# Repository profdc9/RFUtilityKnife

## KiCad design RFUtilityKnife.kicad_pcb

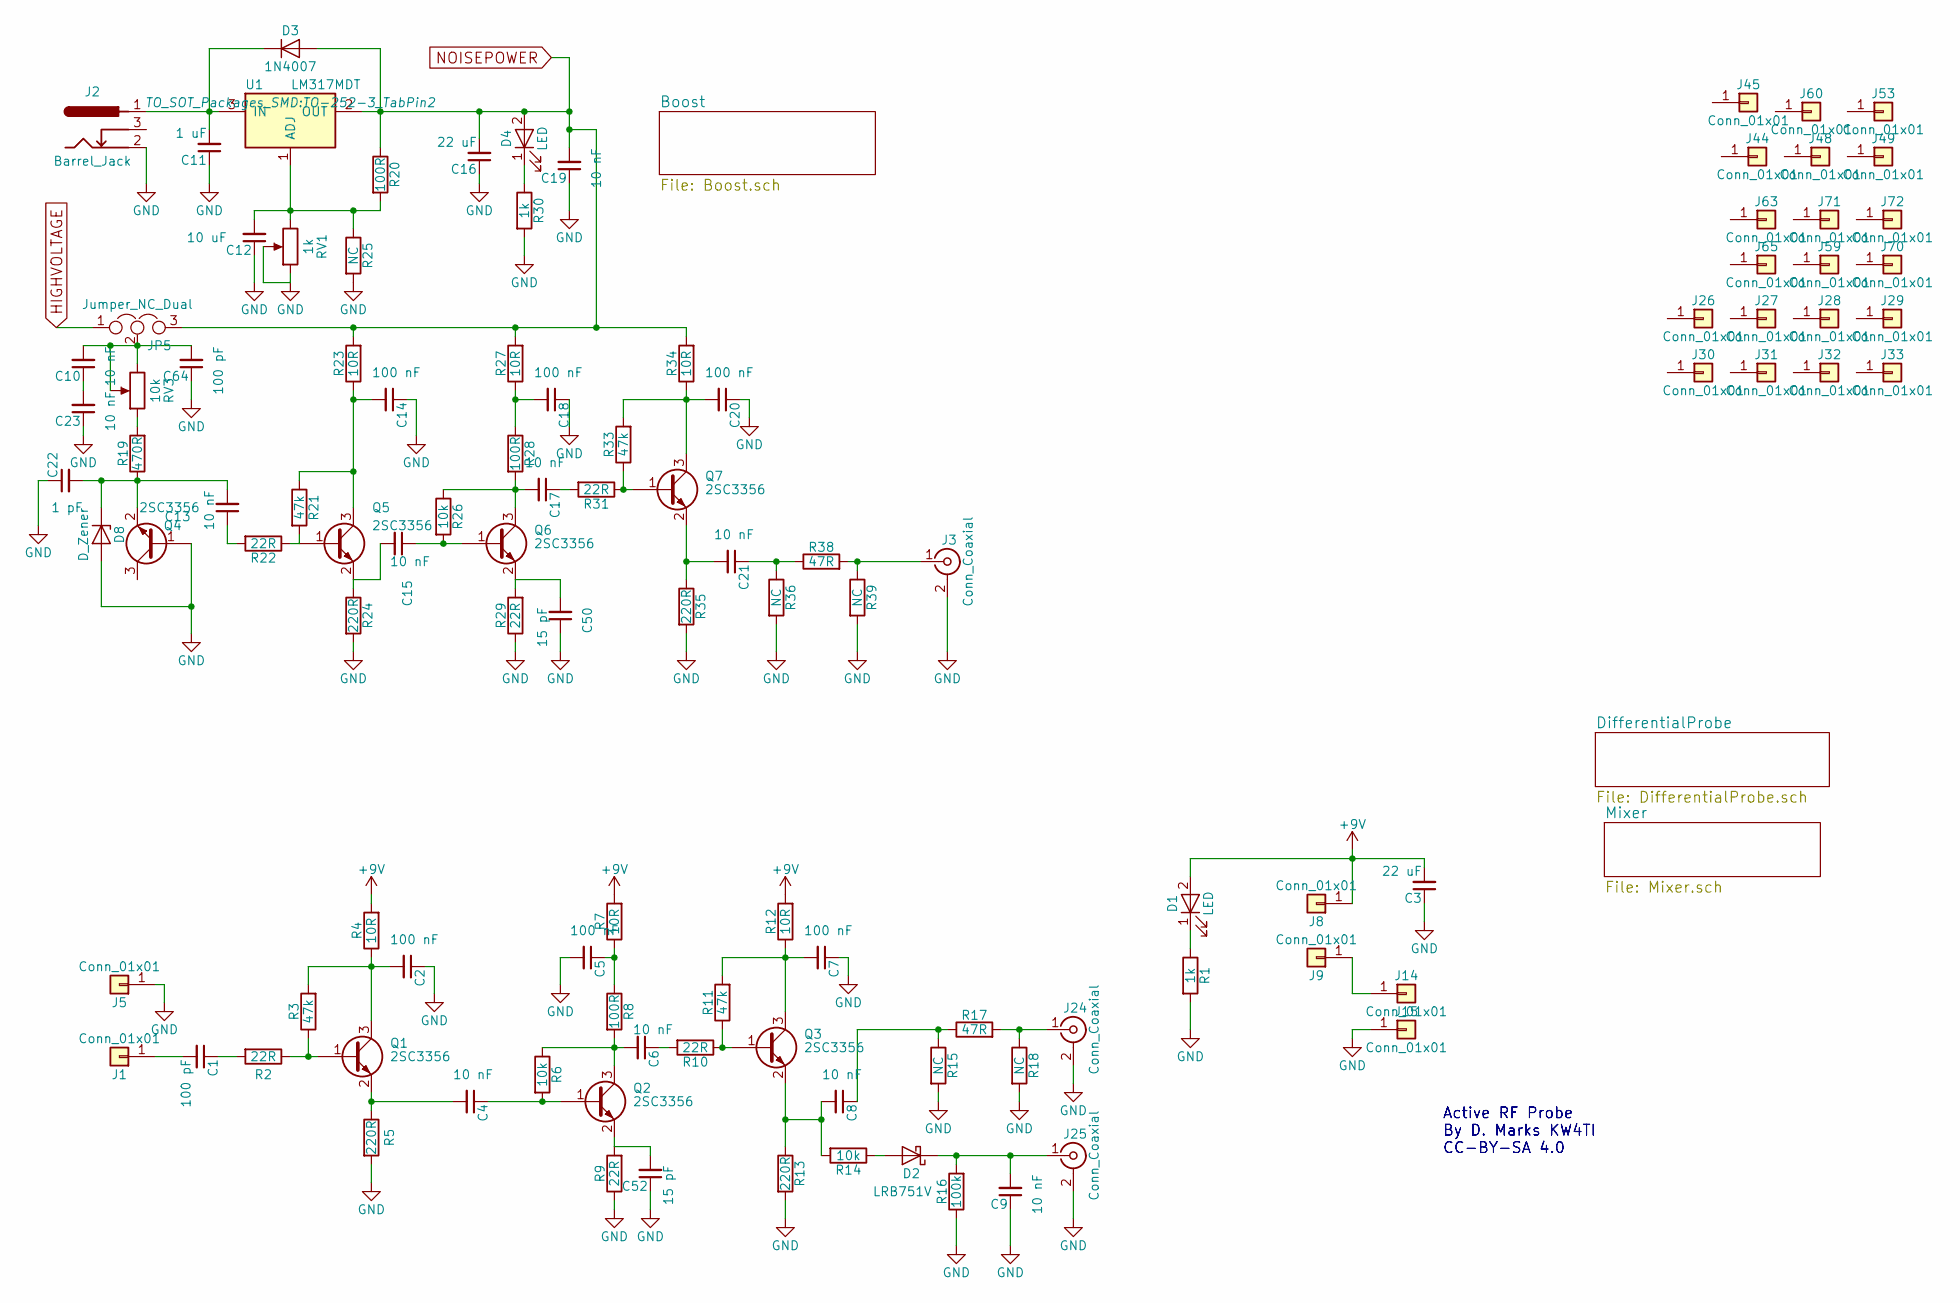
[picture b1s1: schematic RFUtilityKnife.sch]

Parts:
C1, C64: 100 pF; C_0805_HandSoldering; LCSC C1790
C2, C5, C7, C14, C18, C20: 100 nF; C_0805_HandSoldering; LCSC C49678
C3, C16: 22 uF; C_0805_HandSoldering; LCSC C45783
C4, C6, C8, C9, C10, C13, C15, C17, C19, C21, C23: 10 nF; C_0805_HandSoldering; LCSC C1710
C11: 1 uF; C_0805_HandSoldering; LCSC C28323
C12: 10 uF; C_0805_HandSoldering; LCSC C15850
C22: 1 pF; C_0805_HandSoldering; LCSC C14971
C50, C52: 15 pF; C_0805_HandSoldering; LCSC C1794
D1, D4: LED; LED_0805_HandSoldering; LCSC C2296
D2: LRB751V; D_SOD-323_HandSoldering; LCSC C131730
D3: 1N4007; D_SMA_Handsoldering; LCSC C95872
D8: D_Zener; D_MiniMELF
J1, J5, J8, J9, J14, J15: Conn_01x01; PadHole
J2: Barrel_Jack; BARREL_JACK
J3, J24, J25: Conn_Coaxial; Amphenol_RF_SMA_132289
J26, J27, J28, J29, J30, J31, J32, J33, J44, J45, J48, J49, J53, J59, J60, J63, J65, J70, J71, J72: Conn_01x01; BigSlot
JP5: Jumper_NC_Dual; Pin_Header_Straight_1x03_Pitch2.54mm
Q1, Q2, Q3, Q4, Q5, Q6, Q7: 2SC3356; SOT-23; LCSC C9659
R1, R30: 1k; R_0805_HandSoldering; LCSC C17513
R2, R9, R10, R22, R29, R31: 22R; R_0805_HandSoldering; LCSC C17561
R3, R11, R21, R33: 47k; R_0805_HandSoldering; LCSC C17713
R4, R7, R12, R23, R27, R34: 10R; R_0805_HandSoldering; LCSC C17415
R5, R13, R24, R35: 220R; R_0805_HandSoldering; LCSC C17557
R6, R14, R26: 10k; R_0805_HandSoldering; LCSC C17414
R8, R20, R28: 100R; R_0805_HandSoldering; LCSC C17408
R15, R18, R25, R36, R39: NC; R_0805_HandSoldering
R16: 100k; R_0805_HandSoldering; LCSC C17407
R17, R38: 47R; R_0805_HandSoldering; LCSC C17714
R19: 470R; R_0805_HandSoldering; LCSC C17710
RV1: 1k; Potentiometer_Triwood_RM-065
RV3: 10k; Potentiometer_Triwood_RM-065
U1: LM317MDT; TO-252-3_TabPin2; LCSC C75510

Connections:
+9V: C3.2, D1.2 (A), J8.1, R4.2, R7.2, R12.2
GND: C2.1, C3.1, C5.2, C7.1, C9.1, C11.1, C12.1, C14.1, C16.1, C18.1, C19.1, C20.1, C22.1, C23.1, C50.1, C52.1, C64.1, D8.2 (A), J2.2, J3.2 (Ext), J5.1, J15.1, J24.2 (Ext), J25.2 (Ext), Q4.1 (B), R1.2, R5.2, R9.1, R13.2, R15.2, R16.1, R18.2, R24.2, R25.2, R29.1, R30.2, R35.2, R36.2, R39.2, RV1.1, RV1.2; also elsewhere on the board
HIGHVOLTAGE: JP5.1; also elsewhere on the board
NOISEPOWER: C16.2, C19.2, D3.2 (A), D4.2 (A), JP5.3, R20.1, R23.2, R27.2, R34.2, U1.2 (OUT); also elsewhere on the board
unnamed: C1.1, R2.2
unnamed: C1.2, J1.1
unnamed: C2.2, Q1.3 (C), R3.2, R4.1
unnamed: C4.1, Q2.1 (B), R6.2
unnamed: C4.2, Q1.2 (E), R5.1
unnamed: C5.1, R7.1, R8.1
unnamed: C6.1, R10.2
unnamed: C6.2, Q2.3 (C), R6.1, R8.2
unnamed: C7.2, Q3.3 (C), R11.2, R12.1
unnamed: C8.1, R15.1, R17.1
unnamed: C8.2, Q3.2 (E), R13.1, R14.2
unnamed: C9.2, D2.1 (K), J25.1 (In), R16.2
unnamed: C10.1, C23.2
unnamed: C10.2, C64.2, JP5.2, RV3.2, RV3.3
unnamed: C11.2, D3.1 (K), J2.1, U1.3 (IN)
unnamed: C12.2, R20.2, R25.1, RV1.3, U1.1 (ADJ)
unnamed: C13.1, R22.2
unnamed: C13.2, C22.2, D8.1 (K), Q4.2 (E), R19.1
unnamed: C14.2, Q5.3 (C), R21.1, R23.1
unnamed: C15.1, Q6.1 (B), R26.2
unnamed: C15.2, Q5.2 (E), R24.1
unnamed: C17.1, R31.2
unnamed: C17.2, Q6.3 (C), R26.1, R28.2
unnamed: C18.2, R27.1, R28.1
unnamed: C20.2, Q7.3 (C), R33.2, R34.1
unnamed: C21.1, R36.1, R38.1
unnamed: C21.2, Q7.2 (E), R35.1
unnamed: C50.2, Q6.2 (E), R29.2
unnamed: C52.2, Q2.2 (E), R9.2
unnamed: D1.1 (K), R1.1
unnamed: D2.2 (A), R14.1
unnamed: D4.1 (K), R30.1
unnamed: J3.1 (In), R38.2, R39.1
unnamed: J9.1, J14.1
unnamed: J24.1 (In), R17.2, R18.1
unnamed: Q1.1 (B), R2.1, R3.1
unnamed: Q3.1 (B), R10.1, R11.1
unnamed: Q5.1 (B), R21.2, R22.1
unnamed: Q7.1 (B), R31.1, R33.1
unnamed: R19.2, RV3.1

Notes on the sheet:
Active RF Probe By D. Marks KW4TI CC-BY-SA 4.0

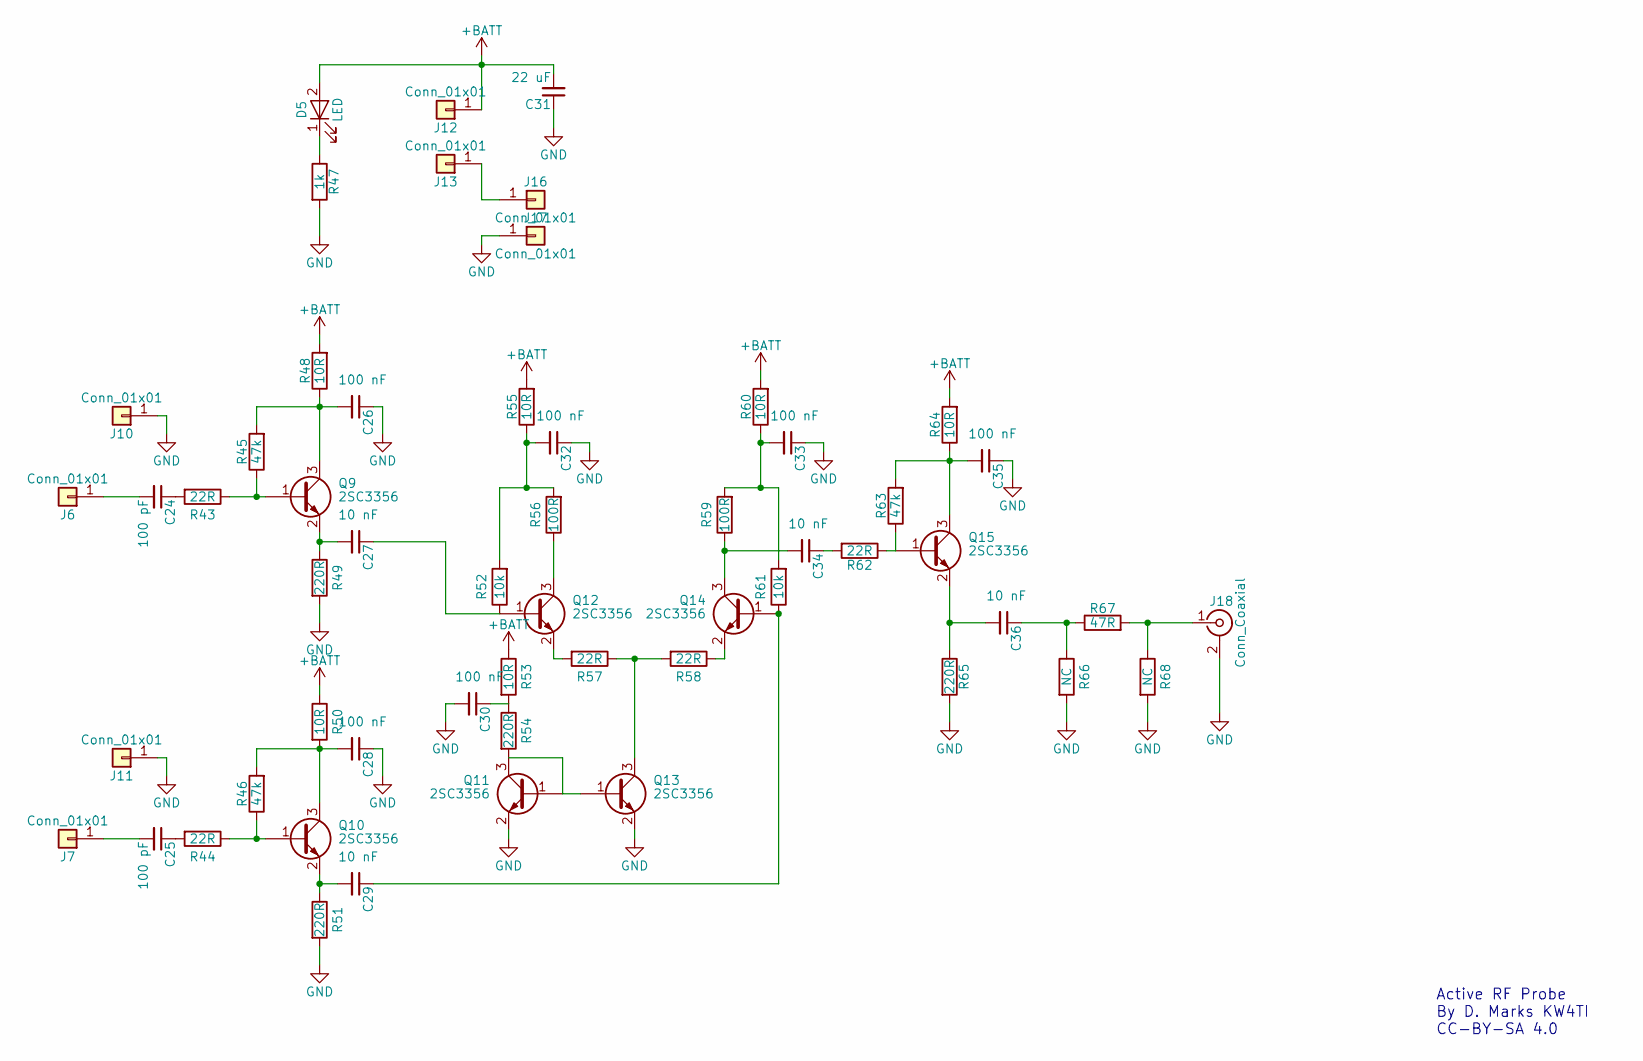
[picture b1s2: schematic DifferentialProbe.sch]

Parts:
C24, C25: 100 pF; C_0805_HandSoldering; LCSC C1790
C26, C28, C30, C32, C33, C35: 100 nF; C_0805_HandSoldering; LCSC C49678
C27, C29, C34, C36: 10 nF; C_0805_HandSoldering; LCSC C1710
C31: 22 uF; C_0805_HandSoldering; LCSC C45783
D5: LED; LED_0805_HandSoldering; LCSC C2296
J6, J7, J10, J11, J12, J13, J16, J17: Conn_01x01; PadHole
J18: Conn_Coaxial; Amphenol_RF_SMA_132289
Q9, Q10, Q11, Q12, Q13, Q14, Q15: 2SC3356; SOT-23; LCSC C9659
R43, R44, R57, R58, R62: 22R; R_0805_HandSoldering; LCSC C17561
R45, R46, R63: 47k; R_0805_HandSoldering; LCSC C17713
R47: 1k; R_0805_HandSoldering; LCSC C17513
R48, R50, R53, R55, R60, R64: 10R; R_0805_HandSoldering; LCSC C17415
R49, R51, R54, R65: 220R; R_0805_HandSoldering; LCSC C17557
R52, R61: 10k; R_0805_HandSoldering; LCSC C17414
R56, R59: 100R; R_0805_HandSoldering; LCSC C17408
R66, R68: NC; R_0805_HandSoldering
R67: 47R; R_0805_HandSoldering; LCSC C17714

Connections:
+BATT: C31.2, D5.2 (A), J12.1, R48.2, R50.1, R53.1, R55.2, R60.2, R64.2
GND: C26.1, C28.1, C30.2, C31.1, C32.1, C33.1, C35.1, J10.1, J11.1, J17.1, J18.2 (Ext), Q11.2 (E), Q13.2 (E), R47.2, R49.2, R51.2, R65.2, R66.2, R68.2; also elsewhere on the board
unnamed: C24.1, R43.2
unnamed: C24.2, J6.1
unnamed: C25.1, R44.2
unnamed: C25.2, J7.1
unnamed: C26.2, Q9.3 (C), R45.2, R48.1
unnamed: C27.1, Q12.1 (B), R52.1
unnamed: C27.2, Q9.2 (E), R49.1
unnamed: C28.2, Q10.3 (C), R46.2, R50.2
unnamed: C29.1, Q14.1 (B), R61.1
unnamed: C29.2, Q10.2 (E), R51.1
unnamed: C30.1, R53.2, R54.1
unnamed: C32.2, R52.2, R55.1, R56.2
unnamed: C33.2, R59.2, R60.1, R61.2
unnamed: C34.1, R62.2
unnamed: C34.2, Q14.3 (C), R59.1
unnamed: C35.2, Q15.3 (C), R63.2, R64.1
unnamed: C36.1, R66.1, R67.1
unnamed: C36.2, Q15.2 (E), R65.1
unnamed: D5.1 (K), R47.1
unnamed: J13.1, J16.1
unnamed: J18.1 (In), R67.2, R68.1
unnamed: Q9.1 (B), R43.1, R45.1
unnamed: Q10.1 (B), R44.1, R46.1
unnamed: Q11.1 (B), Q11.3 (C), Q13.1 (B), R54.2
unnamed: Q12.2 (E), R57.2
unnamed: Q12.3 (C), R56.1
unnamed: Q13.3 (C), R57.1, R58.2
unnamed: Q14.2 (E), R58.1
unnamed: Q15.1 (B), R62.1, R63.1

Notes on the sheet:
Active RF Probe By D. Marks KW4TI CC-BY-SA 4.0

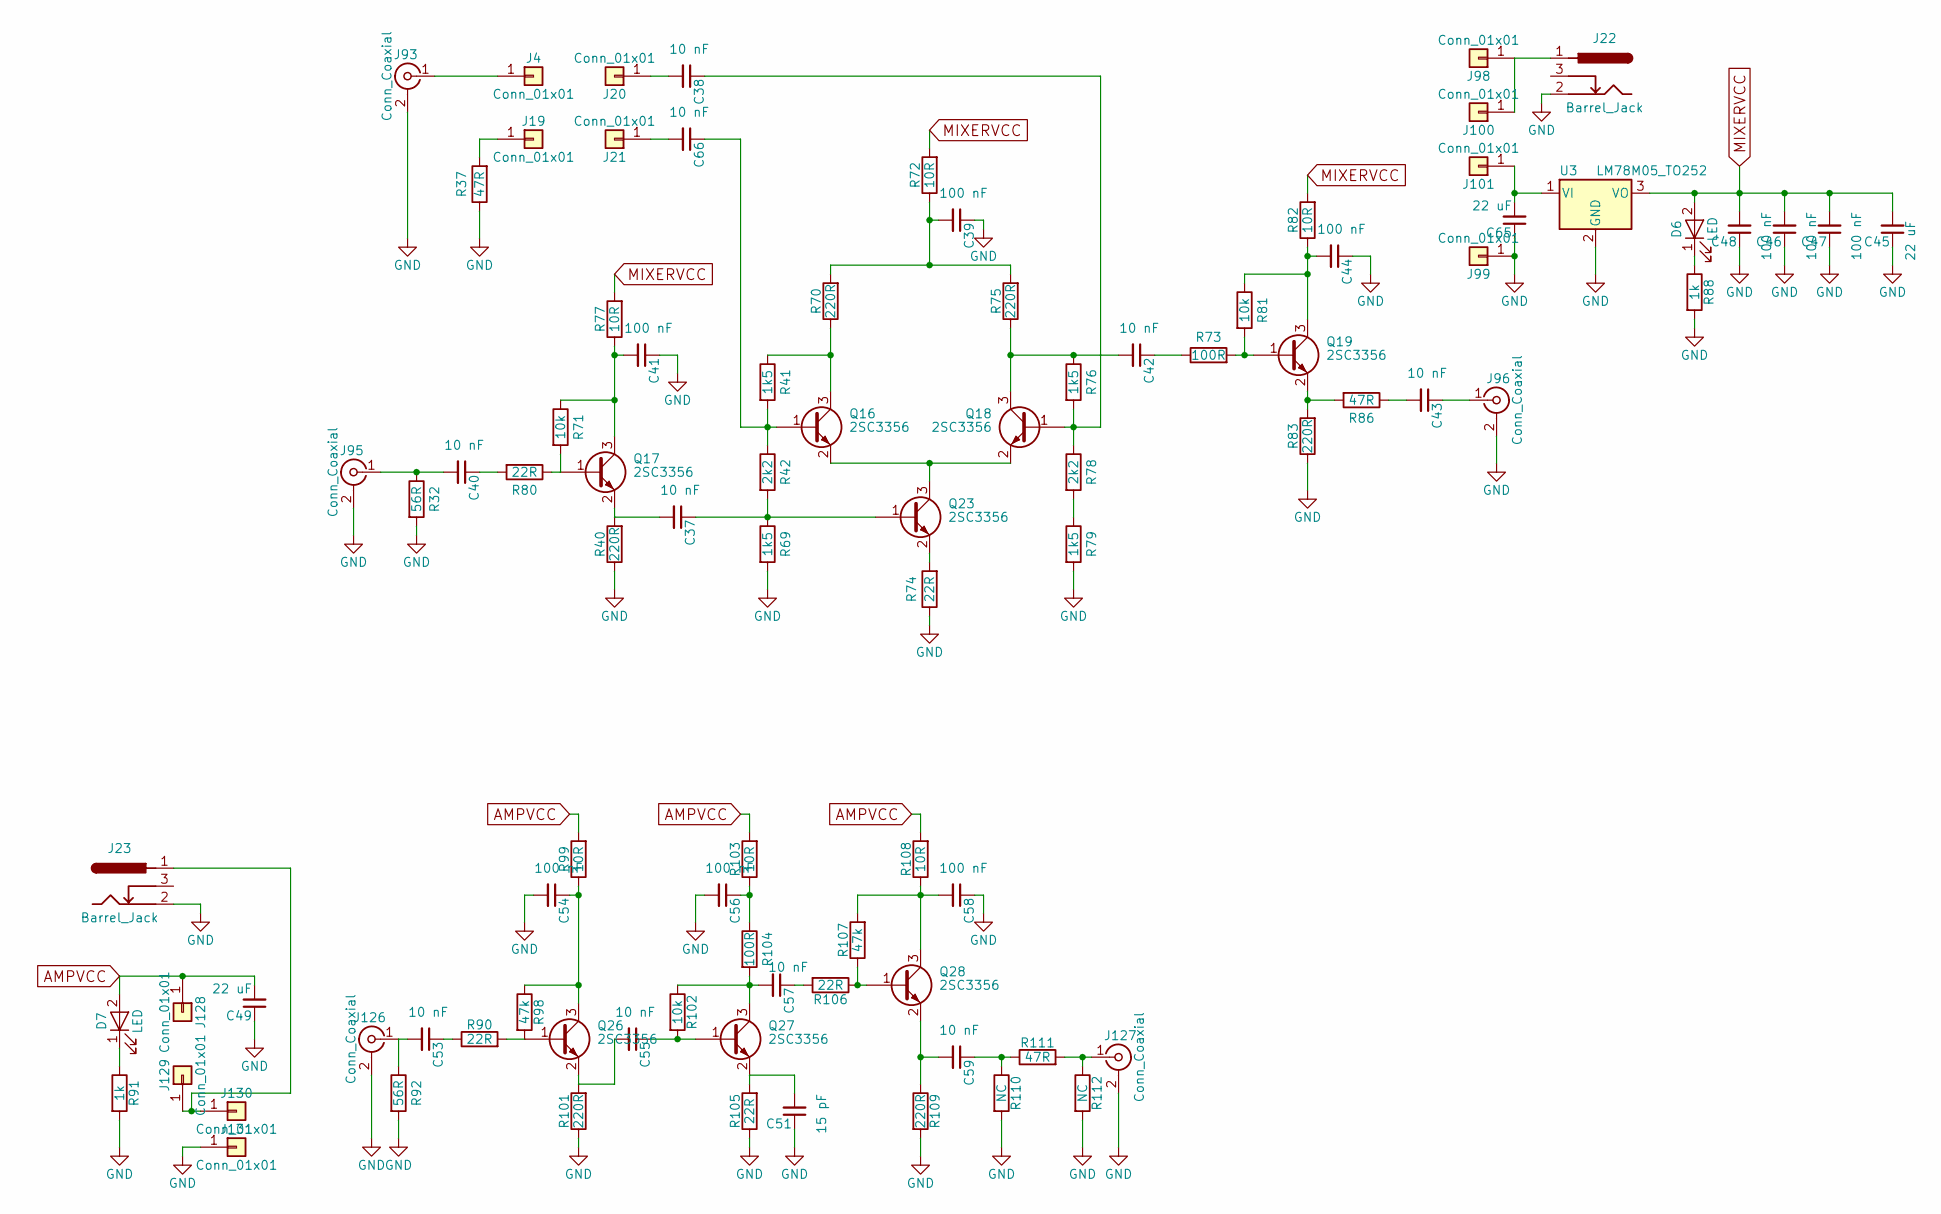
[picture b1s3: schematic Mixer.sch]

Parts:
C37, C38, C40, C42, C43, C53, C55, C57, C59, C66: 10 nF; C_0805_HandSoldering; LCSC C1710
C39, C41, C44, C46, C47, C48, C54, C56, C58: 100 nF; C_0805_HandSoldering; LCSC C49678
C45, C49, C65: 22 uF; C_0805_HandSoldering; LCSC C45783
C51: 15 pF; C_0805_HandSoldering; LCSC C1794
D6, D7: LED; LED_0805_HandSoldering; LCSC C2296
J4, J19, J20, J21, J98, J99, J100, J101, J128, J129, J130, J131: Conn_01x01; PadHole
J22, J23: Barrel_Jack; BARREL_JACK
J93, J95, J96, J126, J127: Conn_Coaxial; Amphenol_RF_SMA_132289
Q16, Q17, Q18, Q19, Q23, Q26, Q27, Q28: 2SC3356; SOT-23; LCSC C9659
R32, R92: 56R; R_0805_HandSoldering; LCSC C17757
R37, R86, R111: 47R; R_0805_HandSoldering; LCSC C17714
R40, R70, R75, R83, R101, R109: 220R; R_0805_HandSoldering; LCSC C17557
R41, R69, R76, R79: 1k5; R_0805_HandSoldering; LCSC C4310
R42, R78: 2k2; R_0805_HandSoldering; LCSC C17520
R71, R81, R102: 10k; R_0805_HandSoldering; LCSC C17414
R72, R77, R82, R99, R103, R108: 10R; R_0805_HandSoldering; LCSC C17415
R73, R104: 100R; R_0805_HandSoldering; LCSC C17408
R74, R80, R90, R105, R106: 22R; R_0805_HandSoldering; LCSC C17561
R88, R91: 1k; R_0805_HandSoldering; LCSC C17513
R98, R107: 47k; R_0805_HandSoldering; LCSC C17713
R110, R112: NC; R_0805_HandSoldering
U3: LM78M05_TO252; TO-252-3_TabPin2; LCSC C58069

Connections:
AMPVCC: C49.2, D7.2 (A), J128.1, R99.2, R103.2, R108.2
GND: C39.1, C41.1, C44.1, C45.1, C46.1, C47.1, C48.1, C49.1, C51.1, C54.2, C56.2, C58.1, C65.1, J22.2, J23.2, J93.2 (Ext), J95.2 (Ext), J96.2 (Ext), J99.1, J126.2 (Ext), J127.2 (Ext), J131.1, R32.2, R37.1, R40.1, R69.2, R74.1, R79.2, R83.1, R88.2, R91.2, R92.2, R101.1, R105.1, R109.2, R110.2, R112.2, U3.2 (GND); also elsewhere on the board
MIXERVCC: C45.2, C46.2, C47.2, C48.2, D6.2 (A), R72.2, R77.2, R82.2, U3.3 (VO)
unnamed: C37.1, Q23.1 (B), R42.2, R69.1
unnamed: C37.2, Q17.2 (E), R40.2
unnamed: C38.1, Q18.1 (B), R76.2, R78.1
unnamed: C38.2, J20.1
unnamed: C39.2, R70.2, R72.1, R75.2
unnamed: C40.1, R80.2
unnamed: C40.2, J95.1 (In), R32.1
unnamed: C41.2, Q17.3 (C), R71.1, R77.1
unnamed: C42.1, R73.1
unnamed: C42.2, Q18.3 (C), R75.1, R76.1
unnamed: C43.1, J96.1 (In)
unnamed: C43.2, R86.1
unnamed: C44.2, Q19.3 (C), R81.1, R82.1
unnamed: C51.2, Q27.2 (E), R105.2
unnamed: C53.1, R90.1
unnamed: C53.2, J126.1 (In), R92.1
unnamed: C54.1, Q26.3 (C), R98.1, R99.1
unnamed: C55.1, Q27.1 (B), R102.2
unnamed: C55.2, Q26.2 (E), R101.2
unnamed: C56.1, R103.1, R104.1
unnamed: C57.1, R106.2
unnamed: C57.2, Q27.3 (C), R102.1, R104.2
unnamed: C58.2, Q28.3 (C), R107.2, R108.1
unnamed: C59.1, R110.1, R111.1
unnamed: C59.2, Q28.2 (E), R109.1
unnamed: C65.2, J101.1, U3.1 (VI)
unnamed: C66.1, Q16.1 (B), R41.2, R42.1
unnamed: C66.2, J21.1
unnamed: D6.1 (K), R88.1
unnamed: D7.1 (K), R91.1
unnamed: J4.1, J93.1 (In)
unnamed: J19.1, R37.2
unnamed: J22.1, J98.1, J100.1
unnamed: J127.1 (In), R111.2, R112.1
unnamed: J23.1, J129.1, J130.1
unnamed: Q16.2 (E), Q18.2 (E), Q23.3 (C)
unnamed: Q16.3 (C), R41.1, R70.1
unnamed: Q17.1 (B), R71.2, R80.1
unnamed: Q19.1 (B), R73.2, R81.2
unnamed: Q19.2 (E), R83.2, R86.2
unnamed: Q23.2 (E), R74.2
unnamed: Q26.1 (B), R90.2, R98.2
unnamed: Q28.1 (B), R106.1, R107.1
unnamed: R78.2, R79.1

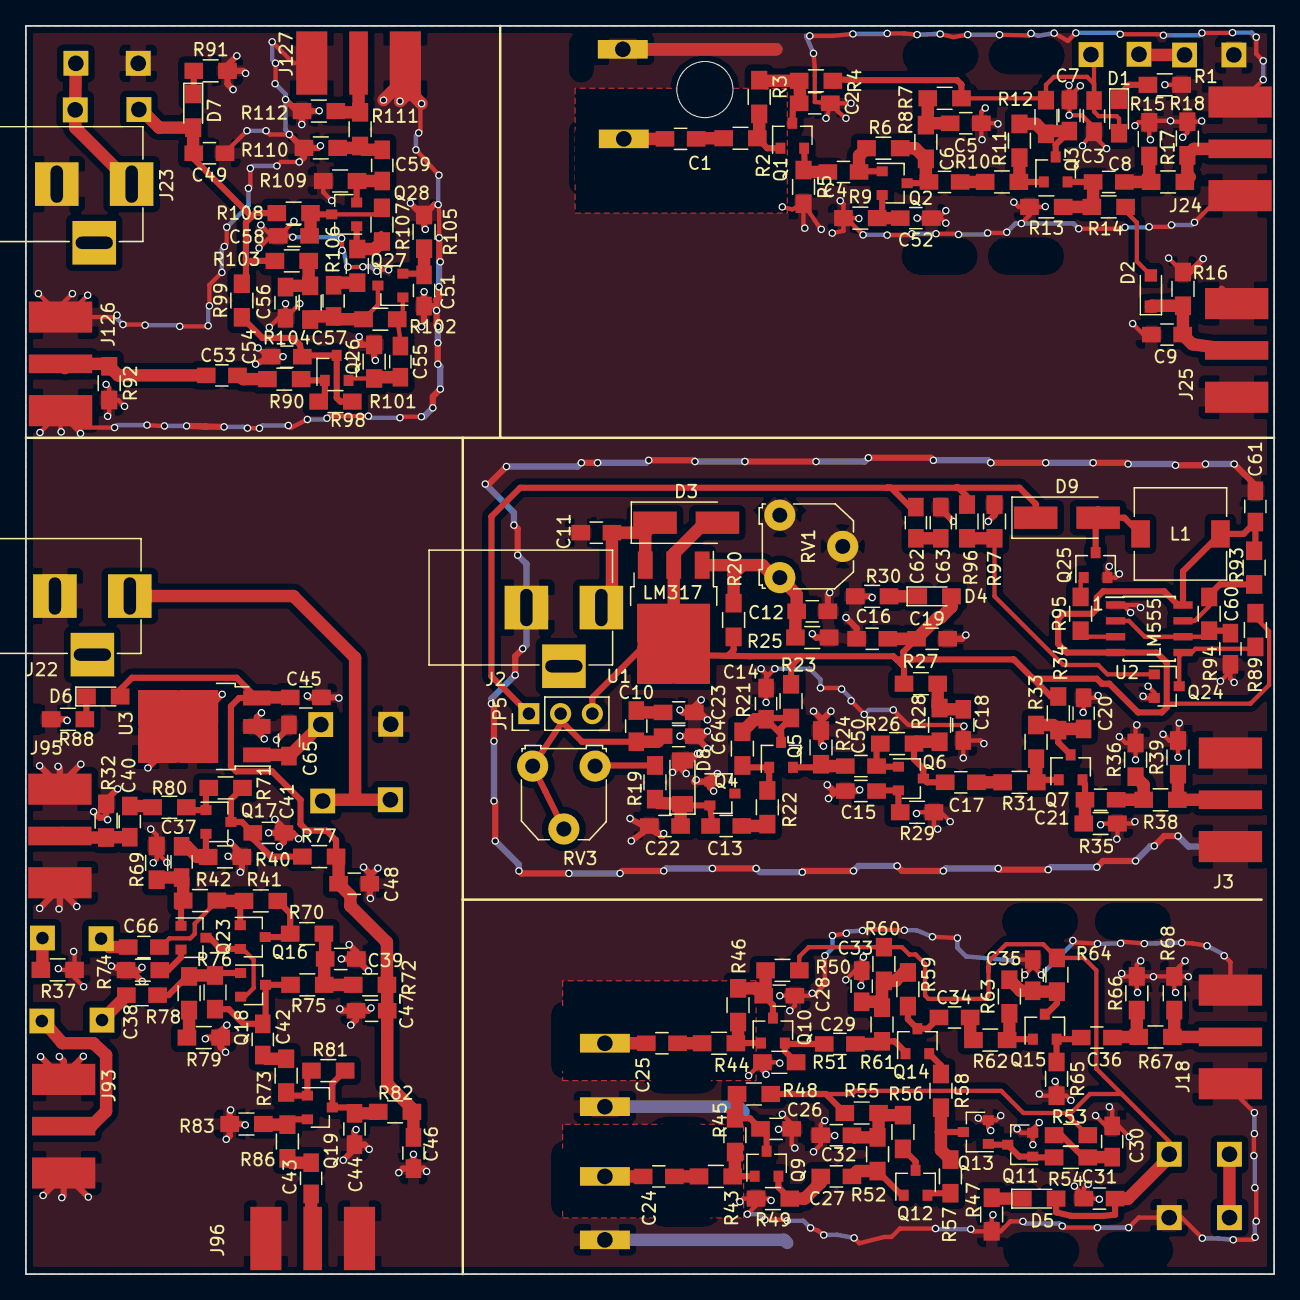
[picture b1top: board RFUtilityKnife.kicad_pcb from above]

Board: 2 copper layers, 100.0 x 100.0 mm, 272 parts (0 on the bottom side), 128 nets.

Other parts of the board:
C60: 100 pF; C_0805_HandSoldering
C61, C62, C63: 2.2 uF; C_0805_HandSoldering
D9: US1MG; D_SMA_Handsoldering
L1: 10 uH; L_7.3x7.3_H4.5
Q24, Q25: MMBT5551; SOT-23
R89: 100k; R_0805_HandSoldering
R93, R95, R97: 1k; R_0805_HandSoldering
R94: 10k; R_0805_HandSoldering
R96: 47k; R_0805_HandSoldering
U2: NE555; SOIC-8_3.9x4.9mm_Pitch1.27mm

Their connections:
GND: C60.2, C61.2, C63.2, Q24.2, Q25.2, R97.2, U2.1; also elsewhere on the board
HIGHVOLTAGE: C62.1, D9.1, R96.1; also elsewhere on the board
NOISEPOWER: C61.1, L1.1, R89.1, R93.2, U2.4, U2.8; also elsewhere on the board
unnamed: C60.1, R94.2, U2.2, U2.6
unnamed: C62.2, C63.1
unnamed: D9.2, L1.2, Q25.3
unnamed: Q24.1, R96.2, R97.1
unnamed: Q24.3, R89.2, U2.5
unnamed: Q25.1, R95.2
unnamed: R93.1, R94.1, U2.7
unnamed: R95.1, U2.3

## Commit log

2020-05-20 JLCPCB order 2020-05-20
2020-05-21 Real actual accepted for production by JLCPCB files, you cant fault a guy for trying
2020-07-13 Submitted to JLCPCB 2020-07-12
